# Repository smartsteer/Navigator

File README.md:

# SmartSteer Navigator

Aplikacja do prowadzenia równoległego i autosterowania ciągnika, zgodna z płytkami AgOpenGPS (AIO).
Jeden kod w Kotlinie daje dwie wersje:

- **Android** — tablet w kabinie (APK),
- **Windows** — komputer / tablet z Windows (instalator `.msi` / `.exe`).

## Jak to działa

Aplikacja liczy geometrię prowadzenia (linia AB, krzywe, pure pursuit) i co ok. 100 ms wysyła
zadany kąt skrętu do modułu na płytce. Regulację silnika (PID, PWM) i odczyt czujnika kąta kół
robi oryginalny firmware AgOpenGPS na płytce — nie jest zmieniany.

Komunikacja: UDP w sieci `192.168.5.x`, aplikacja nasłuchuje na porcie **9999**, wysyła na **8888**.
Ramka: `0x80 0x81 źródło PGN długość dane… CRC`.

| PGN | Kierunek | Treść |
|-----|----------|-------|
| 254 | aplikacja → moduł skrętu | prędkość, autoster wł./wył., kąt zadany, odległość od linii, sekcje |
| 253 | moduł skrętu → aplikacja | kąt rzeczywisty, kurs/przechył IMU, przełączniki, PWM |
| 252 / 251 | aplikacja → moduł skrętu | ustawienia i konfiguracja sterowania |
| 239 | aplikacja → moduł maszyny | sekcje, podnośnik, zawrót |

### Podłączenie tabletu z Androidem

Przejściówka USB‑C → Ethernet (najlepiej hub z ładowaniem PD) albo Wi‑Fi przez mały router
w kabinie. Router powinien rozdawać adresy (DHCP) w sieci `192.168.5.x`.

## Struktura

```
composeApp/
  src/commonMain/   wspólny kod: logika (core/) i ekrany (Compose Multiplatform)
  src/androidMain/  start aplikacji na Androidzie
  src/desktopMain/  start programu na Windowsie
  src/commonTest/   testy
```

## Budowanie

- Android: `./gradlew :composeApp:assembleDebug`
- Windows (na Windowsie): `./gradlew :composeApp:packageMsi`
- Uruchomienie na komputerze bez instalacji: `./gradlew :composeApp:run`
- Testy: `./gradlew :composeApp:desktopTest`

GitHub Actions budują APK i instalator Windows przy każdym pushu — pliki są w zakładce
**Actions → ostatni przebieg → Artifacts**.

## Plan

1. Rdzeń: odczyt NMEA, linia AB, odchyłka, symulator jazdy
2. Autosterowanie: pure pursuit, PGN 254/253, ekran diagnostyki
3. Sekcje i mapa pokrycia, zawroty, granice pól
4. Integracja z WAR (mapy aplikacyjne, ewidencja zabiegów)

## Licencja

GNU General Public License v3.0 (GPLv3). Projekt korzysta z rozwiązań i algorytmów AgOpenGPS
(© Brian Tischler i współtwórcy, GPLv3) — fragmenty przeniesione z AgOpenGPS są oznaczone w kodzie.
Program rozpowszechniany jest z kodem źródłowym, na tej samej licencji.

WAR (Wirtualny Asystent Rolnika) jest osobnym programem i nie jest objęty tą licencją —
wymienia dane z Navigatorem przez interfejs (mapy dawek, ewidencja zabiegów).

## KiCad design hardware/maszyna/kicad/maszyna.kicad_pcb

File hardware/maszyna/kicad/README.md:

# Płytka Maszyna — projekt KiCad 7

| Plik | Co to |
|---|---|
| `maszyna.py` | schemat jako kod (SKiDL) — źródło prawdy; `python3 maszyna.py` → `maszyna.net` + `piny.tsv` |
| `maszyna.net` | netlista KiCad (279 elementów) |
| `maszyna.kicad_pro` / `.kicad_pcb` | projekt i płytka: 165 × 120 mm, 4 warstwy (F.Cu sygnały, In1 masa, In2 +12 V, B.Cu sygnały), elementy **rozmieszczone, bez ścieżek** |
| `place.py` / `netclass.py` | skrypty rozmieszczenia i klas połączeń (Moc20A 3 mm, Moc2A 1 mm, Zasilanie 0,6 mm) |
| `review.py` → `../przeglad_schematu.pdf` | raport połączeń do przeglądu (pin → sieć → z czym połączony) |
| `smartsteer.pretty` | footprint AMPSEAL 35 (wyprowadzony z 23‑pin — sprawdzić z rysunkiem TE 776231) |

## Stan (2026-11-12)

- Schemat (netlista) kompletny, ERC bez błędów poza znanym (V3 CH340C na 3,3 V — zgodnie z kartą).
- Rozmieszczenie automatyczne w strefach: kostki AMPSEAL przy przedniej krawędzi, 8 × DRV8962 w rzędzie pod nimi, rejestry,
  zasilanie i lampy na dole, ESP32 z anteną przy prawej krawędzi (strefa zakazu miedzi), GPS, USB‑C, CAN, ADC po prawej.
- **Ścieżek brak** — automatyczny router (Freerouting) nie mógł zostać uruchomiony w środowisku, w którym powstał projekt.
  Do zrobienia: ścieżki (ręcznie albo Freerouting: Plik → Eksport → Specctra DSN, potem import SES),
  polygony 20–30 A na F.Cu/B.Cu dla VIN_RAW → Q1 → V12 i U8 → LAMPA_OUT → J2 7–8 (miedź 2 oz),
  wylanie masy na F.Cu/B.Cu, DRC, potem pliki do JLCPCB (Gerber, wiercenia, BOM, CPL).

## Ścieżki automatem (Freerouting) — u siebie, ok. 10 minut

`maszyna.dsn` jest gotowy (wyeksportowany bez wylewek masy na F.Cu/B.Cu — warstwy wewnętrzne to płaszczyzny GND i V12).

1. Zainstaluj Javę 21 i pobierz Freerouting z https://github.com/freerouting/freerouting/releases (plik `freerouting-*.jar`).
2. `java -jar freerouting.jar -de maszyna.dsn -do maszyna.ses -mp 25`
   (w DSN są już klasy: Moc20A 3 mm — VIN_RAW, V12, V12_ZAWORY, LAMPA_OUT; Moc2A 1 mm — sekcje, zawory, rezerwa; Zasilanie 0,6 mm.
   GPS_RF jest poprowadzony ręcznie 0,36 mm i zablokowany. Pary USB_DP/USB_DM i CANH/CANL najlepiej poprowadzić ręcznie —
   w GUI Freeroutingu można je odznaczyć przed routingiem.)
3. KiCad → otwórz `maszyna.kicad_pcb` → Plik → Import → Specctra Session → `maszyna.ses`.
4. Dodaj wylewki masy na F.Cu i B.Cu (B: wypełnij strefy), sprawdź DRC, popraw ścieżki mocy (polygony 20–30 A).
5. Plik → Fabrication Outputs → Gerbers + Drill; BOM/CPL do JLCPCB.

## Przegląd zewnętrzny 2026-11-12 — co zmieniono, co nie

Wprowadzone:
- GPS (L76K): zasilanie VCC/V_BCKP przez koralik ferrytowy 600 Ω + 10 µF + 100 nF (sieć V3V3_GPS).
- ADS1115: zasilanie przez filtr RC 10 Ω + 1 µF (V3V3_ADC).
- Pomiar prądu lamp: R_IS 2,2 kΩ (20 A → ~2,0 V), do ADC przez 10 kΩ + 100 nF (ochrona przy sygnale błędu na IS).
- Nazwy sieci pompy ładunkowej DRV8962: DRVk_VCP / DRVk_CPL / DRVk_CPH (wcześniej mylące Uk_…).

Nie zmieniono (uzasadnienie):
- OCPM do DVDD: wg karty TI stan wysoki = **automatyczny restart** po przeciążeniu (stan niski = zatrzaśnięcie) — zostawione;
  firmware i tak czyta nFAULT przez 74HC165 i może dać impuls nSLEEP.
- GPS_BIAS: zasilanie anteny aktywnej idzie z pinu **VDD_RF** modułu (wyjście = VCC) przez 10 Ω i 47 nH do RF_IN —
  połączenie z V3V3 nie jest potrzebne (do potwierdzenia w L76K Hardware Design).
- Dławik CMC na CAN — opcjonalny; do decyzji przy długiej wiązce (pinout dławika trzeba wtedy sprawdzić z kartą).
- Footprint J2 „P0.4mm” to nazwa z biblioteki KiCad; pady faktycznie co 4,0 mm.

## Wytyczne do prowadzenia ścieżek (z przeglądu)

- VIN_RAW (J2 1–3 → Q1, D1) i V12 do U8/mostków: wylewki 5–8 mm na F.Cu i B.Cu, przelotki co 3–4 mm; LAMPA_OUT (U8 piny 5–7 → J2 7–8): wylewka ≥ 4–5 mm.
- Wyjścia mostków: 3 piny OUTx połączone szerokim polem przy układzie, dalej 1,2–1,5 mm; diody TVS przy pinach złączy.
- Pod padem każdego DRV8962: 18–24 przelotki termiczne (0,3/0,6 mm) do masy i odkryta maska od spodu; pod LMR33610 6–9 przelotek.
- Kondensatory 10 nF / 10 µF przy pinach VM–PGND, 100 nF CPH–CPL i 1 µF VCP–VM tuż przy pinach 1, 43, 44.
- Przetwornica: zwarta pętla Cin → VIN → SW → L1 → Cout → GND; BUCK_FB z dala od L1 i węzła SW.
- GPS_RF (U10 pin 11 → J7): 50 Ω, ok. 0,35–0,38 mm przy prepregu 0,2 mm nad masą (sprawdzić w kalkulatorze JLCPCB dla wybranego stosu), bez przelotek, płot z przelotek GND.
- USB_DP/DM para 90 Ω, CANH/CANL para 120 Ω. Antena ESP32 poza miedzią wszystkich warstw (strefa zakazu jest w projekcie).
- Masa jedna, ciągła (In1) — bez cięcia; podział stref fizyczny: moc (dół/środek, złącza), cyfrowe/RF (prawa strona).

## Sprzętowy PWM (przegląd 2026-11-12)

- ~~Mostek 16 z PWM~~ — wycofane: silnik może brać do 15 A, a DRV8962 daje 2 A / 5 A szczytowo. Zamiast tego osobny
  **mostek silnika 15 A**: DRV8701E + 4 × BUK7J1R4‑40H, EN = PWM z IO14 (impulsy IO14 przy starcie nieszkodliwe: nSLEEP = 0 i EN ściągnięte),
  PH = IO15, nFAULT = IO34, prąd przez bocznik 3 mΩ → SO → AIN3, wyjście końcówki M4 → Deutsch DTP 2‑pin.
- Zasilanie główne przez Deutsch DTP 2‑pin → końcówki M4 (X1/X2), idealna dioda na dwóch MOSFET‑ach równolegle.
- Klucz lamp U8 (IO25) obsługuje PWM 200 Hz–1 kHz bez zmian na płytce (silnik jednokierunkowy dużej mocy, pomiar prądu AIN2).
- Uwagi z przeglądu nie wprowadzone: IO27 i IO33 nie są wolne (dioda czerwona, CAN RX); F1 i zworki nie nachodzą na inne
  elementy — `crtyd.py` liczy przecięcia courtyardów: 0 (F1 ma 0,7 mm odstępu od U20/U22, zworki są co 8 mm).

## Przegląd 2026-11-12 (mostek silnika) — odpowiedzi

- F1 nie nachodzi na U20: pady F1 kończą się na y = 55,0 mm, pady U20 zaczynają na 56,5 mm (courtyardy bez przecięcia — `crtyd.py`).
- Oznaczenia: Q1, Q2 = idealna dioda; Q3, Q4 = MMBT3904 (auto‑reset); Q5–Q8 = mostek silnika. Aktualna lista z płytki: `../bom_jlcpcb.csv`
  (generowana z netlisty — `bom.csv` ma opisy i MPN, oznaczenia tam orientacyjne).
- DRV8701E: footprint VQFN‑24 4 × 4 mm, pad termiczny 2,45 × 2,45 mm z przelotkami (wg przeglądu; potwierdzić z rysunkiem TI RGE).
- IO15 (MTDO) jako kierunek silnika: stan przy starcie wycisza tylko logi ROM, nie blokuje startu.
- Obudowa: okna pod gniazda panelowe DTP04‑2P prostokątne (20,5 × 24,5 mm, parametr `dtp_okno`) — dopasować do wariantu (np. ‑L012) z rysunku TE.

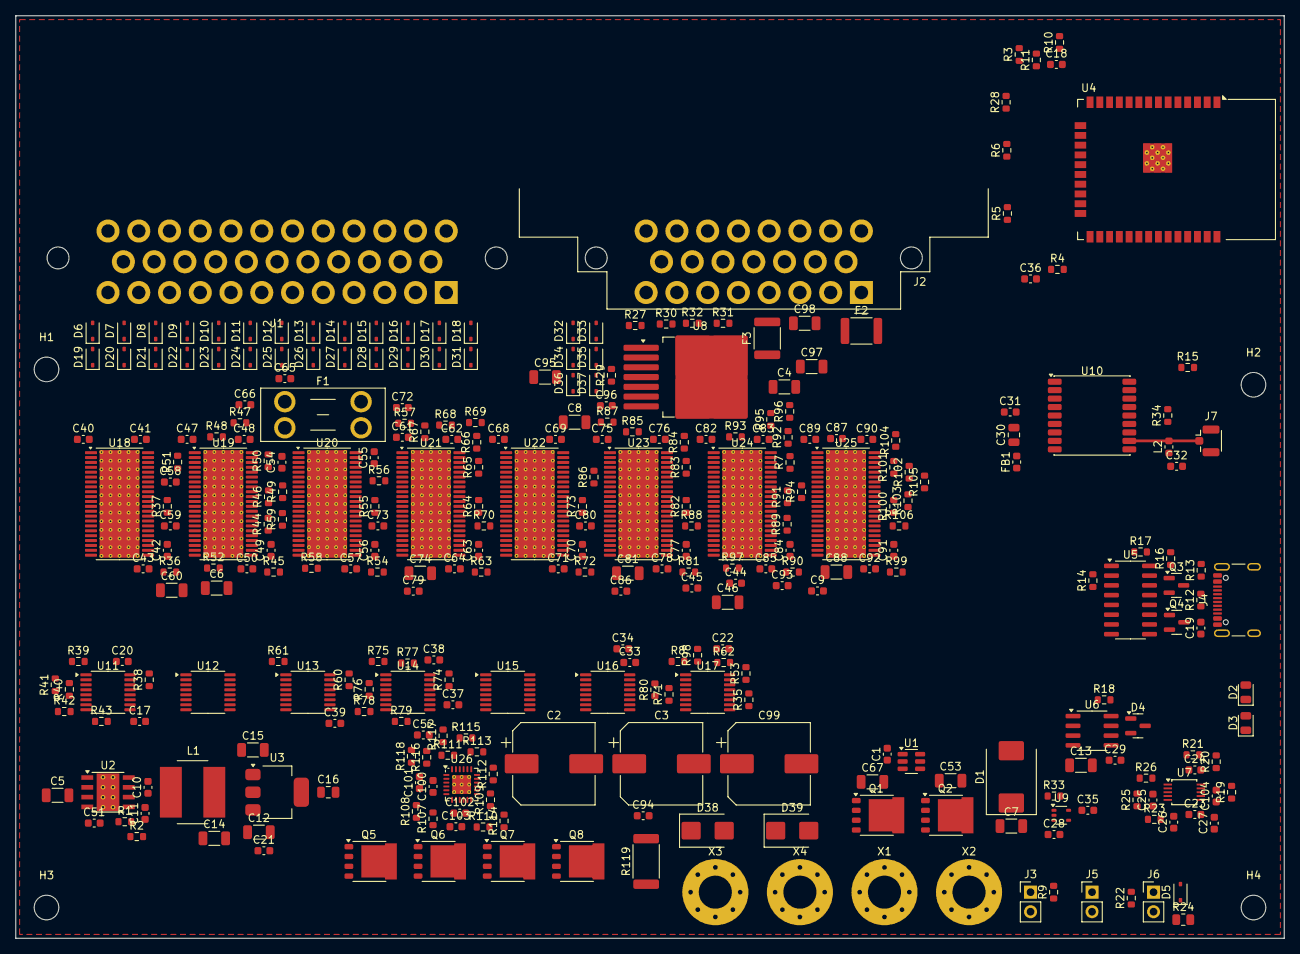
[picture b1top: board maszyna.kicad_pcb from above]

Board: 4 copper layers, 165.0 x 120.0 mm, 317 parts (0 on the bottom side), 222 nets.

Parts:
C1, C10, C17, C19, C20, C21, C22, C24, C25, C26, C27, C29, C31, C32, C33, C34, C35, C36, C37, C38, C39, C43, C50, C57, C64, C71, C78, C85, C92: 100n; C_0603_1608Metric
C2, C3, C99: 220u 35V 105°C; CP_Elec_10x10.5
C4, C5, C6, C7, C8, C46, C53, C60, C67, C74, C81, C88, C95, C97, C98: 10u 50V; C_1206_3216Metric
C9, C41, C48, C55, C62, C69, C76, C83, C90, C96, C101: 100n 50V; C_0603_1608Metric
C11, C18, C23, C42, C49, C56, C63, C70, C77, C84, C91, C102, C103: 1u; C_0603_1608Metric
C12, C13, C14, C15: 22u 10V; C_1206_3216Metric
C16, C30: 10u; C_0805_2012Metric
C28, C104: 1n; C_0603_1608Metric
C40, C47, C54, C61, C68, C75, C82, C89, C100: 1u 16V; C_0603_1608Metric
C44, C45, C51, C52, C58, C59, C65, C66, C72, C73, C79, C80, C86, C87, C93, C94: 10n 50V; C_0603_1608Metric
D1: SMDJ26A; D_SMC
D2: LED zielona; LED_0805_2012Metric
D3: LED czerwona; LED_0805_2012Metric
D4: PESD2CAN; SOT-23
D5: PESD5V0S1BA; D_SOD-323
D6, D7, D8, D9, D10, D11, D12, D13, D14, D15, D16, D17, D18, D19, D20, D21, D22, D23, D24, D25, D26, D27, D28, D29, D30, D31, D32, D33, D34, D35, D36, D37: PESD24VS1UL; D_SOD-323
D38, D39: SMBJ26CA; D_SMB
F1: 10A mini; Fuseholder_Blade_Mini_Keystone_3568
F2: 0.2A; Fuse_1812_4532Metric
F3: 0.5A; Fuse_1812_4532Metric
FB1: 600R@100MHz; L_0603_1608Metric
H1, H2, H3, H4: MountingHole_3.2mm_M3
J1: AMPSEAL 35 (sekcje); TE_AMPSEAL_776231-1_3Rows_35_P4mm_Horizontal
J2: AMPSEAL 23 (zasilanie, czujniki); TE_AMPSEAL_1-776087-x_3Rows_23_P0.4mm_Horizontal
J3: JP CAN/BT; PinHeader_1x02_P2.54mm_Vertical
J4: USB-C; USB_C_Receptacle_GCT_USB4105-xx-A_16P_TopMnt_Horizontal
J5: JP terminator CAN; PinHeader_1x02_P2.54mm_Vertical
J6: JP 4-20mA; PinHeader_1x02_P2.54mm_Vertical
J7: U.FL → SMA; U.FL_Hirose_U.FL-R-SMT-1_Vertical
L1: 10uH 2A; L_Bourns_SRN8040TA
L2: 47nH; L_0603_1608Metric
Q1, Q2, Q5, Q6, Q7, Q8: BUK7J1R4-40H; LFPAK56
Q3, Q4: MMBT3904; SOT-23
R1, R7, R25, R115, R116, R117, R118: 100k; R_0603_1608Metric
R2: 24k9; R_0603_1608Metric
R3, R4, R5, R6, R8, R9, R16, R17, R22, R26, R30, R32, R35, R36, R37, R38, R39, R40, R41, R42, R43, R44, R45, R46, R47, R48, R49, R50, R51, R52, R53, R54, R55, R56, R57, R58, R59, R60, R61, R62, R63, R64, R65, R66, R67, R68, R69, R70, R71, R72, R73, R74, R75, R76, R77, R78, R79, R80, R81, R82, R83, R84, R85, R86, R87, R88, R89, R90, R91, R92, R93, R94, R95, R96, R97, R98, R99, R100, R101, R102, R103, R104, R105, R106, R108, R110, R111, R112, R113: 10k; R_0603_1608Metric
R10, R11, R114: 1k; R_0603_1608Metric
R12, R13: 5k1; R_0603_1608Metric
R14, R15: 470; R_0603_1608Metric
R18: 120; R_0603_1608Metric
R19, R34: 10; R_0603_1608Metric
R20, R21, R28, R31, R33: 4k7; R_0603_1608Metric
R23: 20k; R_0603_1608Metric
R24: 150 0.1%; R_0805_2012Metric
R27: 47; R_0603_1608Metric
R29: 2k2; R_0603_1608Metric
R107: 22k; R_0603_1608Metric
R109: 200k; R_0603_1608Metric
R119: 3m 3W; R_2512_6332Metric
U1: LM74700-Q1; SOT-23-6
U2: LMR33610ADDAR; Texas_HSOP-8-1EP_3.9x4.9mm_P1.27mm_ThermalVias
U3: AMS1117-3.3; SOT-223-3_TabPin2
U4: ESP32-WROOM-32E-N8; ESP32-WROOM-32D
U5: CH340C; SOIC-16_3.9x9.9mm_P1.27mm
U6: TJA1051T/3; SOIC-8_3.9x4.9mm_P1.27mm
U7: ADS1115IDGSR; TSSOP-10_3x3mm_P0.5mm
U8: BTS50015-1TAD; TO-263-7_TabPin4
U9: 74LVC1G17; SOT-353_SC-70-5
U10: Quectel L76K; Quectel_L76
U11, U12, U13, U14, U15, U16: 74HC595PW-Q100; TSSOP-16_4.4x5mm_P0.65mm
U17: 74HC165PW-Q100; TSSOP-16_4.4x5mm_P0.65mm
U18, U19, U20, U21, U22, U23, U24, U25: DRV8962QDDWRQ1; HTSSOP-44-1EP_6.1x14mm_P0.635mm_EP5.2x14mm_Mask4.31x8.26mm_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
U26: DRV8701ERGER; VQFN-24-1EP_4x4mm_P0.5mm_EP2.45x2.45mm_ThermalVias
X1: M4 VIN+ (DTP zasilanie); MountingHole_4.3mm_M4_Pad_Via
X2: M4 GND (DTP zasilanie); MountingHole_4.3mm_M4_Pad_Via
X3: M4 SILNIK A (DTP silnik); MountingHole_4.3mm_M4_Pad_Via
X4: M4 SILNIK B (DTP silnik); MountingHole_4.3mm_M4_Pad_Via

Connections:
ADC_AIN0: C25.1, R22.2, R23.1, U7.4
ADC_AIN1: C26.1, R25.2, R26.1, U7.5
ADC_AIN2: C27.1, R30.2, U7.6
ADC_AIN3: C104.1, R114.2, U7.7
AR_B1: Q3.1, R16.2
AR_B2: Q4.1, R17.2
BUCK_BOOT: C10.1, U2.7
BUCK_FB: R1.2, R2.1, U2.5
BUCK_SW: C10.2, L1.1, U2.8
BUCK_VCC: C11.1, U2.6
CANH: D4.1, J2.19, R18.1, U6.7
CANL: D4.2, J2.20, J5.2, U6.6
CAN_RX: U4.9, U6.4
CAN_TERM: J5.1, R18.2
CAN_TX: U4.8, U6.1
CISN_SHUNT: J6.2, R24.1
CISN_SYG: D5.1, J2.17, J6.1, R22.1
DRV0_CPH: C41.1, U18.44
DRV0_CPL: C41.2, U18.43
DRV0_DVDD: C42.1, C43.1, R36.1, U18.24, U18.25, U18.27
DRV0_VCP: C40.1, U18.1
DRV0_VREF: R36.2, R37.1, U18.33
DRV0_nFAULT: R35.2, U17.11, U18.26
DRV1_CPH: C48.1, U19.44
DRV1_CPL: C48.2, U19.43
DRV1_DVDD: C49.1, C50.1, R45.1, U19.24, U19.25, U19.27
DRV1_VCP: C47.1, U19.1
DRV1_VREF: R45.2, R46.1, U19.33
DRV1_nFAULT: R44.2, U17.12, U19.26
DRV2_CPH: C55.1, U20.44
DRV2_CPL: C55.2, U20.43
DRV2_DVDD: C56.1, C57.1, R54.1, U20.24, U20.25, U20.27
DRV2_VCP: C54.1, U20.1
DRV2_VREF: R54.2, R55.1, U20.33
DRV2_nFAULT: R53.2, U17.13, U20.26
DRV3_CPH: C62.1, U21.44
DRV3_CPL: C62.2, U21.43
DRV3_DVDD: C63.1, C64.1, R63.1, U21.24, U21.25, U21.27
DRV3_VCP: C61.1, U21.1
DRV3_VREF: R63.2, R64.1, U21.33
DRV3_nFAULT: R62.2, U17.14, U21.26
DRV4_CPH: C69.1, U22.44
DRV4_CPL: C69.2, U22.43
DRV4_DVDD: C70.1, C71.1, R72.1, U22.24, U22.25, U22.27
DRV4_VCP: C68.1, U22.1
DRV4_VREF: R72.2, R73.1, U22.33
DRV4_nFAULT: R71.2, U17.3, U22.26
DRV5_CPH: C76.1, U23.44
DRV5_CPL: C76.2, U23.43
DRV5_DVDD: C77.1, C78.1, R81.1, U23.24, U23.25, U23.27
DRV5_VCP: C75.1, U23.1
DRV5_VREF: R81.2, R82.1, U23.33
DRV5_nFAULT: R80.2, U17.4, U23.26
DRV6_CPH: C83.1, U24.44
DRV6_CPL: C83.2, U24.43
DRV6_DVDD: C84.1, C85.1, R90.1, U24.24, U24.25, U24.27
DRV6_VCP: C82.1, U24.1
DRV6_VREF: R90.2, R91.1, U24.33
DRV6_nFAULT: R89.2, U17.5, U24.26
DRV7_CPH: C90.1, U25.44
DRV7_CPL: C90.2, U25.43
DRV7_DVDD: C91.1, C92.1, R99.1, U25.24, U25.25, U25.27
DRV7_VCP: C89.1, U25.1
DRV7_VREF: R99.2, R100.1, U25.33
DRV7_nFAULT: R98.2, U17.6, U25.26
DRV_nSLEEP: R7.1, U4.26, U18.42, U19.42, U20.42, U21.42, U22.42, U23.42, U24.42, U25.42, U26.13
ESP_EN: C18.1, Q3.3, R3.2, U4.3
ESP_IO0: Q4.3, R4.2, U4.25
ESP_IO2: R5.1, U4.24
ESP_IO12: R6.1, U4.14
FLOW_3V3: U4.7, U9.4
FLT_PL: R8.2, U4.16, U17.1
GND: C2.2, C3.2, C4.2, C5.2, C6.2, C7.2, C8.2, C9.2, C11.2, C12.2, C13.2, C14.2, C15.2, C16.2, C17.2, C18.2, C19.2, C20.2, C21.2, C22.2, C23.2, C24.2, C25.2, C26.2, C27.2, C28.2, C29.2, C30.2, C31.2, C32.2, C33.2, C34.2, C35.2, C36.2, C37.2, C38.2, C39.2, C42.2, C43.2, C44.2, C45.2, C46.2, C49.2, C50.2, C51.2, C52.2, C53.2, C56.2, C57.2, C58.2, C59.2, C60.2, C63.2, C64.2, C65.2, C66.2, C67.2, C70.2, C71.2, C72.2, C73.2, C74.2, C77.2, C78.2, C79.2, C80.2, C81.2, C84.2, C85.2, C86.2, C87.2, C88.2, C91.2, C92.2, C93.2, C94.2, C95.2, C96.2, C97.2, C98.2, C99.2, C102.2, C103.2, C104.2, D1.2, D2.1, D3.1, D4.3, D5.2, D6.2, D7.2, D8.2, D9.2, D10.2, D11.2, D12.2, D13.2, D14.2, D15.2, D16.2, D17.2, D18.2, D19.2, D20.2, D21.2, D22.2, D23.2, D24.2, D25.2, D26.2, D27.2, D28.2, D29.2, D30.2, D31.2, D32.2, D33.2, D34.2, D35.2, D36.2, D37.2, D38.2, D39.2, J1.31, J1.32, J1.33, J1.34, J1.35, J2.4, J2.5, J2.6, J2.15, J2.18, J2.23, J3.2, J4.A1, J4.A12, J4.B1, J4.B12, J4.S1, J7.2, R2.2, R5.2, R6.2, R7.2, R12.2, R13.2, R23.2, R24.2, R26.2, R27.2, R29.2, R33.2, R37.2, R38.2, R39.2, R40.2, R41.2, R42.2, R43.2, R46.2, R47.2, R48.2, R49.2, R50.2, R51.2, R52.2, R55.2, R56.2, R57.2, R58.2, R59.2, R60.2, R61.2, R64.2, R65.2, R66.2, R67.2, R68.2, R69.2, R70.2, R73.2, R74.2, R75.2, R76.2, R77.2, R78.2, R79.2, R82.2, R83.2, R84.2, R85.2, R86.2, R87.2, R88.2, R91.2, R92.2, R93.2, R94.2, R95.2, R96.2, R97.2, R100.2, R101.2, R102.2, R103.2, R104.2, R105.2, R106.2, R108.2, R109.2, R112.2, R113.2, R119.2, U1.2, U2.1, U2.9, U3.1, U4.1, U4.15, U4.38, U4.39, U5.1, U6.2, U6.8, U7.1, U7.3, U9.3, U10.1, U10.10, U10.12, U11.8, U11.13, U12.8, U12.13, U13.8, U13.13, U14.8, U14.13, U15.8, U15.13, U16.8, U16.13, U17.8, U17.10, U17.15, U18.3, U18.10, U18.13, U18.20, U18.22, U18.23, U18.28, U18.29, U18.30, U18.31, U18.32, U18.45, U19.3, U19.10, U19.13, U19.20, U19.22, U19.23, U19.28, U19.29, U19.30, U19.31, U19.32, U19.45, U20.3, U20.10, U20.13, U20.20, U20.22, U20.23, U20.28, U20.29, U20.30, U20.31, U20.32, U20.45, U21.3, U21.10, U21.13, U21.20, U21.22, U21.23, U21.28, U21.29, U21.30, U21.31, U21.32, U21.45, U22.3, U22.10, U22.13, U22.20, U22.22, U22.23, U22.28, U22.29, U22.30, U22.31, U22.32, U22.45, U23.3, U23.10, U23.13, U23.20, U23.22, U23.23, U23.28, U23.29, U23.30, U23.31, U23.32, U23.45, U24.3, U24.10, U24.13, U24.20, U24.22, U24.23, U24.28, U24.29, U24.30, U24.31, U24.32, U24.45, U25.3, U25.10, U25.13, U25.20, U25.22, U25.23, U25.28, U25.29, U25.30, U25.31, U25.32, U25.45, U26.5, U26.16, U26.20, U26.25, X2.1
GPS_BIAS: C32.1, L2.1, R34.2
GPS_RF: J7.1, L2.2, U10.11
GPS_RXD: U4.28, U10.3
GPS_TXD: U4.27, U10.2
GPS_VDD_RF: R34.1, U10.14
I2C_SCL: R21.2, U4.36, U7.10
I2C_SDA: R20.2, U4.33, U7.9
ID_GATE: Q1.4, Q2.4, U1.5
ID_VCAP: C1.1, U1.1
JP_CAN: J3.1, R9.2, U4.4
LAMPA_OUT: J2.7, J2.8, U8.5, U8.6, U8.7
LAMP_GND: R27.1, U8.1
LAMP_IN: R28.1, U4.10
LAMP_IS: R29.1, R30.1, U8.3
LED_A_czerwona: D3.2, R11.2
LED_A_zielona: D2.2, R10.2
LED_CZERWONA: R11.1, U4.12
LED_ZIELONA: R10.1, U4.11
M1_EN: R40.1, U11.2, U18.36, U18.37
M1_INA: R38.1, U11.15, U18.41
M1_INB: R39.1, U11.1, U18.40
M2_EN: R43.1, U11.5, U18.34, U18.35
M2_INA: R41.1, U11.3, U18.39
M2_INB: R42.1, U11.4, U18.38
M3_EN: R49.1, U12.15, U19.36, U19.37
M3_INA: R47.1, U11.6, U19.41
M3_INB: R48.1, U11.7, U19.40
M4_EN: R52.1, U12.3, U19.34, U19.35
M4_INA: R50.1, U12.1, U19.39
M4_INB: R51.1, U12.2, U19.38
M5_EN: R58.1, U12.6, U20.36, U20.37
M5_INA: R56.1, U12.4, U20.41
M5_INB: R57.1, U12.5, U20.40
M6_EN: R61.1, U13.1, U20.34, U20.35
M6_INA: R59.1, U12.7, U20.39
M6_INB: R60.1, U13.15, U20.38
M7_EN: R67.1, U13.4, U21.36, U21.37
M7_INA: R65.1, U13.2, U21.41
M7_INB: R66.1, U13.3, U21.40
M8_EN: R70.1, U13.7, U21.34, U21.35
M8_INA: R68.1, U13.5, U21.39
M8_INB: R69.1, U13.6, U21.38
M9_EN: R76.1, U14.2, U22.36, U22.37
M9_INA: R74.1, U14.15, U22.41
M9_INB: R75.1, U14.1, U22.40
M10_EN: R79.1, U14.5, U22.34, U22.35
M10_INA: R77.1, U14.3, U22.39
M10_INB: R78.1, U14.4, U22.38
M11_EN: R85.1, U15.15, U23.36, U23.37
M11_INA: R83.1, U14.6, U23.41
M11_INB: R84.1, U14.7, U23.40
M12_EN: R88.1, U15.3, U23.34, U23.35
M12_INA: R86.1, U15.1, U23.39
M12_INB: R87.1, U15.2, U23.38
M13_EN: R94.1, U15.6, U24.36, U24.37
M13_INA: R92.1, U15.4, U24.41
M13_INB: R93.1, U15.5, U24.40
M14_EN: R97.1, U16.1, U24.34, U24.35
M14_INA: R95.1, U15.7, U24.39
M14_INB: R96.1, U16.15, U24.38
M15_EN: R103.1, U16.4, U25.36, U25.37
M15_INA: R101.1, U16.2, U25.41
M15_INB: R102.1, U16.3, U25.40
M16_EN: R106.1, U16.7, U25.34, U25.35
M16_INA: R104.1, U16.5, U25.39
M16_INB: R105.1, U16.6, U25.38
MOT_AVDD: C102.1, R107.1, U26.7
MOT_CPH: C101.1, U26.3
MOT_CPL: C101.2, U26.4
MOT_DIR: R113.1, U4.23, U26.15
MOT_DVDD: C103.1, R110.1, U26.8
MOT_GH1: Q5.4, R115.1, U26.17
MOT_GH2: Q7.4, R117.1, U26.24
MOT_GL1: Q6.4, R116.1, U26.19
MOT_GL2: Q8.4, R118.1, U26.22
MOT_PWM: R112.1, U4.13, U26.14
MOT_SNSOUT: R110.2, U26.10
MOT_SO: R114.1, U26.11
MOT_VCP: C100.1, U26.2
MOT_VREF: R107.2, R108.1, U26.6
MOT_nFAULT: R111.2, U4.6, U26.9
unnamed: J4.A5, R12.1
unnamed: J4.B5, R13.1
unnamed: R14.1, U5.2
unnamed: R15.2, U5.3
unnamed: F2.2, J2.16
unnamed: R28.2, U8.2
unnamed: F3.2, J2.13, R31.1
unnamed: R109.1, U26.12
PRZEPL_DZ: C28.1, R32.2, R33.1, U9.2
PRZEPL_SYG: J2.14, R31.2, R32.1
REG_RCLK: U4.29, U11.12, U12.12, U13.12, U14.12, U15.12, U16.12
REZERWA_A: D36.1, J2.21, U25.17, U25.18, U25.19
REZERWA_B: D37.1, J2.22, U25.14, U25.15, U25.16
SEKCJA1_A: D6.1, J1.1, U18.4, U18.5, U18.6
SEKCJA1_B: D7.1, J1.2, U18.7, U18.8, U18.9
SEKCJA2_A: D8.1, J1.3, U18.17, U18.18, U18.19
SEKCJA2_B: D9.1, J1.4, U18.14, U18.15, U18.16
SEKCJA3_A: D10.1, J1.5, U19.4, U19.5, U19.6
SEKCJA3_B: D11.1, J1.6, U19.7, U19.8, U19.9
SEKCJA4_A: D12.1, J1.7, U19.17, U19.18, U19.19
SEKCJA4_B: D13.1, J1.8, U19.14, U19.15, U19.16
SEKCJA5_A: D14.1, J1.9, U20.4, U20.5, U20.6
SEKCJA5_B: D15.1, J1.10, U20.7, U20.8, U20.9
SEKCJA6_A: D16.1, J1.11, U20.17, U20.18, U20.19
SEKCJA6_B: D17.1, J1.12, U20.14, U20.15, U20.16
SEKCJA7_A: D18.1, J1.13, U21.4, U21.5, U21.6
SEKCJA7_B: D19.1, J1.14, U21.7, U21.8, U21.9
SEKCJA8_A: D20.1, J1.15, U21.17, U21.18, U21.19
SEKCJA8_B: D21.1, J1.16, U21.14, U21.15, U21.16
SEKCJA9_A: D22.1, J1.17, U22.4, U22.5, U22.6
SEKCJA9_B: D23.1, J1.18, U22.7, U22.8, U22.9
SEKCJA10_A: D24.1, J1.19, U22.17, U22.18, U22.19
SEKCJA10_B: D25.1, J1.20, U22.14, U22.15, U22.16
SEKCJA11_A: D26.1, J1.21, U23.4, U23.5, U23.6
SEKCJA11_B: D27.1, J1.22, U23.7, U23.8, U23.9
SEKCJA12_A: D28.1, J1.23, U23.17, U23.18, U23.19
SEKCJA12_B: D29.1, J1.24, U23.14, U23.15, U23.16
SEKCJA13_A: D30.1, J1.25, U24.4, U24.5, U24.6
SEKCJA13_B: D31.1, J1.26, U24.7, U24.8, U24.9
SILNIK_A: D38.1, Q5.1, Q5.2, Q5.3, Q6.5, R115.2, U26.18, X3.1
SILNIK_B: D39.1, Q7.1, Q7.2, Q7.3, Q8.5, R117.2, U26.23, X4.1
SILNIK_BOCZNIK: Q6.1, Q6.2, Q6.3, Q8.1, Q8.2, Q8.3, R116.2, R118.2, R119.1, U26.21
SPI_MISO: U4.31, U17.9
SPI_MOSI: U4.37, U11.14
SPI_SCK: U4.30, U11.11, U12.11, U13.11, U14.11, U15.11, U16.11, U17.2
SR_CHAIN0: U11.9, U12.14
SR_CHAIN1: U12.9, U13.14
SR_CHAIN2: U13.9, U14.14
SR_CHAIN3: U14.9, U15.14
SR_CHAIN4: U15.9, U16.14
U0RXD: R14.2, U4.34
U0TXD: R15.1, U4.35
USB_DM: J4.A7, J4.B7, U5.6
USB_DP: J4.A6, J4.B6, U5.5
USB_DTR: Q4.2, R16.1, U5.13
USB_RTS: Q3.2, R17.1, U5.14
USB_VBUS: C19.1, J4.A4, J4.A9, J4.B4, J4.B9
V3V3: C15.1, C16.1, C17.1, C20.1, C22.1, C29.1, C33.1, C34.1, C35.1, C36.1, C37.1, C38.1, C39.1, FB1.1, R3.1, R4.1, R8.1, R9.1, R19.1, R20.1, R21.1, R35.1, R44.1, R53.1, R62.1, R71.1, R80.1, R89.1, R98.1, R111.1, U3.2, U4.2, U5.4, U5.16, U6.5, U9.5, U11.10, U11.16, U12.10, U12.16, U13.10, U13.16, U14.10, U14.16, U15.10, U15.16, U16.10, U16.16, U17.16
V3V3_ADC: C23.1, C24.1, R19.2, U7.8
V3V3_GPS: C30.1, C31.1, FB1.2, U10.6, U10.8
V5: C12.1, C13.1, C14.1, C21.1, F2.1, L1.2, R1.1, U3.3, U6.3
V12: C2.1, C3.1, C4.1, C5.1, C6.1, C7.1, C8.1, C9.1, C40.2, C44.1, C45.1, C46.1, C47.2, C51.1, C52.1, C53.1, C54.2, C58.1, C59.1, C60.1, C61.2, C65.1, C66.1, C67.1, C68.2, C72.1, C73.1, C74.1, C75.2, C79.1, C80.1, C81.1, C82.2, C86.1, C87.1, C88.1, C89.2, C93.1, C94.1, C95.1, C96.1, C97.1, C98.1, C99.1, C100.2, D1.1, F1.1, F3.1, Q1.5, Q2.5, Q5.5, Q7.5, R25.1, U1.4, U2.2, U2.3, U8.4, U18.2, U18.11, U18.12, U18.21, U19.2, U19.11, U19.12, U19.21, U20.2, U20.11, U20.12, U20.21, U21.2, U21.11, U21.12, U21.21, U22.2, U22.11, U22.12, U22.21, U23.2, U23.11, U23.12, U23.21, U24.2, U24.11, U24.12, U24.21, U25.2, U25.11, U25.12, U25.21, U26.1
V12_ZAWORY: F1.2, J1.27, J1.28, J1.29, J1.30
VIN_RAW: C1.2, J2.1, J2.2, J2.3, Q1.1, Q1.2, Q1.3, Q2.1, Q2.2, Q2.3, U1.3, U1.6, X1.1
ZAW_GLOWNY_A: D32.1, J2.9, U24.17, U24.18, U24.19
ZAW_GLOWNY_B: D33.1, J2.10, U24.14, U24.15, U24.16
ZAW_REG_A: D34.1, J2.11, U25.4, U25.5, U25.6
ZAW_REG_B: D35.1, J2.12, U25.7, U25.8, U25.9

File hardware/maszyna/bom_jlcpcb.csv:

Comment,Designator,Footprint,Quantity
100n,"C1,C10,C17,C19,C20,C21,C22,C24,C25,C26,C27,C29,C31,C32,C33,C34,C35,C36,C37,C38,C39,C43,C50,C57,C64,C71,C78,C85,C92",C_0603_1608Metric,29
220u 35V 105°C,"C2,C3,C99",CP_Elec_10x10.5,3
10u 50V,"C4,C5,C6,C7,C8,C46,C53,C60,C67,C74,C81,C88,C95,C97,C98",C_1206_3216Metric,15
100n 50V,"C9,C41,C48,C55,C62,C69,C76,C83,C90,C96,C101",C_0603_1608Metric,11
1u,"C11,C18,C23,C42,C49,C56,C63,C70,C77,C84,C91,C102,C103",C_0603_1608Metric,13
22u 10V,"C12,C13,C14,C15",C_1206_3216Metric,4
10u,"C16,C30",C_0805_2012Metric,2
1n,"C28,C104",C_0603_1608Metric,2
1u 16V,"C40,C47,C54,C61,C68,C75,C82,C89,C100",C_0603_1608Metric,9
10n 50V,"C44,C45,C51,C52,C58,C59,C65,C66,C72,C73,C79,C80,C86,C87,C93,C94",C_0603_1608Metric,16
SMDJ26A,D1,D_SMC,1
LED zielona,D2,LED_0805_2012Metric,1
LED czerwona,D3,LED_0805_2012Metric,1
PESD2CAN,D4,SOT-23,1
PESD5V0S1BA,D5,D_SOD-323,1
PESD24VS1UL,"D6,D7,D8,D9,D10,D11,D12,D13,D14,D15,D16,D17,D18,D19,D20,D21,D22,D23,D24,D25,D26,D27,D28,D29,D30,D31,D32,D33,D34,D35,D36,D37",D_SOD-323,32
SMBJ26CA,"D38,D39",D_SMB,2
10A mini,F1,Fuseholder_Blade_Mini_Keystone_3568,1
0.2A,F2,Fuse_1812_4532Metric,1
0.5A,F3,Fuse_1812_4532Metric,1
600R@100MHz,FB1,L_0603_1608Metric,1
AMPSEAL 35 (sekcje),J1,TE_AMPSEAL_776231-1_3Rows_35_P4mm_Horizontal,1
"AMPSEAL 23 (zasilanie, czujniki)",J2,TE_AMPSEAL_1-776087-x_3Rows_23_P0.4mm_Horizontal,1
JP CAN/BT,J3,PinHeader_1x02_P2.54mm_Vertical,1
USB-C,J4,USB_C_Receptacle_GCT_USB4105-xx-A_16P_TopMnt_Horizontal,1
JP terminator CAN,J5,PinHeader_1x02_P2.54mm_Vertical,1
JP 4-20mA,J6,PinHeader_1x02_P2.54mm_Vertical,1
U.FL → SMA,J7,U.FL_Hirose_U.FL-R-SMT-1_Vertical,1
10uH 2A,L1,L_Bourns_SRN8040TA,1
47nH,L2,L_0603_1608Metric,1
BUK7J1R4-40H,"Q1,Q2,Q5,Q6,Q7,Q8",LFPAK56,6
MMBT3904,"Q3,Q4",SOT-23,2
100k,"R1,R7,R25,R115,R116,R117,R118",R_0603_1608Metric,7
24k9,R2,R_0603_1608Metric,1
10k,"R3,R4,R5,R6,R8,R9,R16,R17,R22,R26,R30,R32,R35,R36,R37,R38,R39,R40,R41,R42,R43,R44,R45,R46,R47,R48,R49,R50,R51,R52,R53,R54,R55,R56,R57,R58,R59,R60,R61,R62,R63,R64,R65,R66,R67,R68,R69,R70,R71,R72,R73,R74,R75,R76,R77,R78,R79,R80,R81,R82,R83,R84,R85,R86,R87,R88,R89,R90,R91,R92,R93,R94,R95,R96,R97,R98,R99,R100,R101,R102,R103,R104,R105,R106,R108,R110,R111,R112,R113",R_0603_1608Metric,89
1k,"R10,R11,R114",R_0603_1608Metric,3
5k1,"R12,R13",R_0603_1608Metric,2
470,"R14,R15",R_0603_1608Metric,2
120,R18,R_0603_1608Metric,1
10,"R19,R34",R_0603_1608Metric,2
4k7,"R20,R21,R28,R31,R33",R_0603_1608Metric,5
20k,R23,R_0603_1608Metric,1
150 0.1%,R24,R_0805_2012Metric,1
47,R27,R_0603_1608Metric,1
2k2,R29,R_0603_1608Metric,1
22k,R107,R_0603_1608Metric,1
200k,R109,R_0603_1608Metric,1
3m 3W,R119,R_2512_6332Metric,1
LM74700-Q1,U1,SOT-23-6,1
LMR33610ADDAR,U2,Texas_HSOP-8-1EP_3.9x4.9mm_P1.27mm_ThermalVias,1
AMS1117-3.3,U3,SOT-223-3_TabPin2,1
ESP32-WROOM-32E-N8,U4,ESP32-WROOM-32D,1
CH340C,U5,SOIC-16_3.9x9.9mm_P1.27mm,1
TJA1051T/3,U6,SOIC-8_3.9x4.9mm_P1.27mm,1
ADS1115IDGSR,U7,TSSOP-10_3x3mm_P0.5mm,1
BTS50015-1TAD,U8,TO-263-7_TabPin4,1
74LVC1G17,U9,SOT-353_SC-70-5,1
Quectel L76K,U10,Quectel_L76,1
74HC595PW-Q100,"U11,U12,U13,U14,U15,U16",TSSOP-16_4.4x5mm_P0.65mm,6
74HC165PW-Q100,U17,TSSOP-16_4.4x5mm_P0.65mm,1
DRV8962QDDWRQ1,"U18,U19,U20,U21,U22,U23,U24,U25",HTSSOP-44-1EP_6.1x14mm_P0.635mm_EP5.2x14mm_Mask4.31x8.26mm_ThermalVias,8
DRV8701ERGER,U26,VQFN-24-1EP_4x4mm_P0.5mm_EP2.45x2.45mm_ThermalVias,1
M4 VIN+ (DTP zasilanie),X1,MountingHole_4.3mm_M4_Pad_Via,1
M4 GND (DTP zasilanie),X2,MountingHole_4.3mm_M4_Pad_Via,1
M4 SILNIK A (DTP silnik),X3,MountingHole_4.3mm_M4_Pad_Via,1
M4 SILNIK B (DTP silnik),X4,MountingHole_4.3mm_M4_Pad_Via,1
